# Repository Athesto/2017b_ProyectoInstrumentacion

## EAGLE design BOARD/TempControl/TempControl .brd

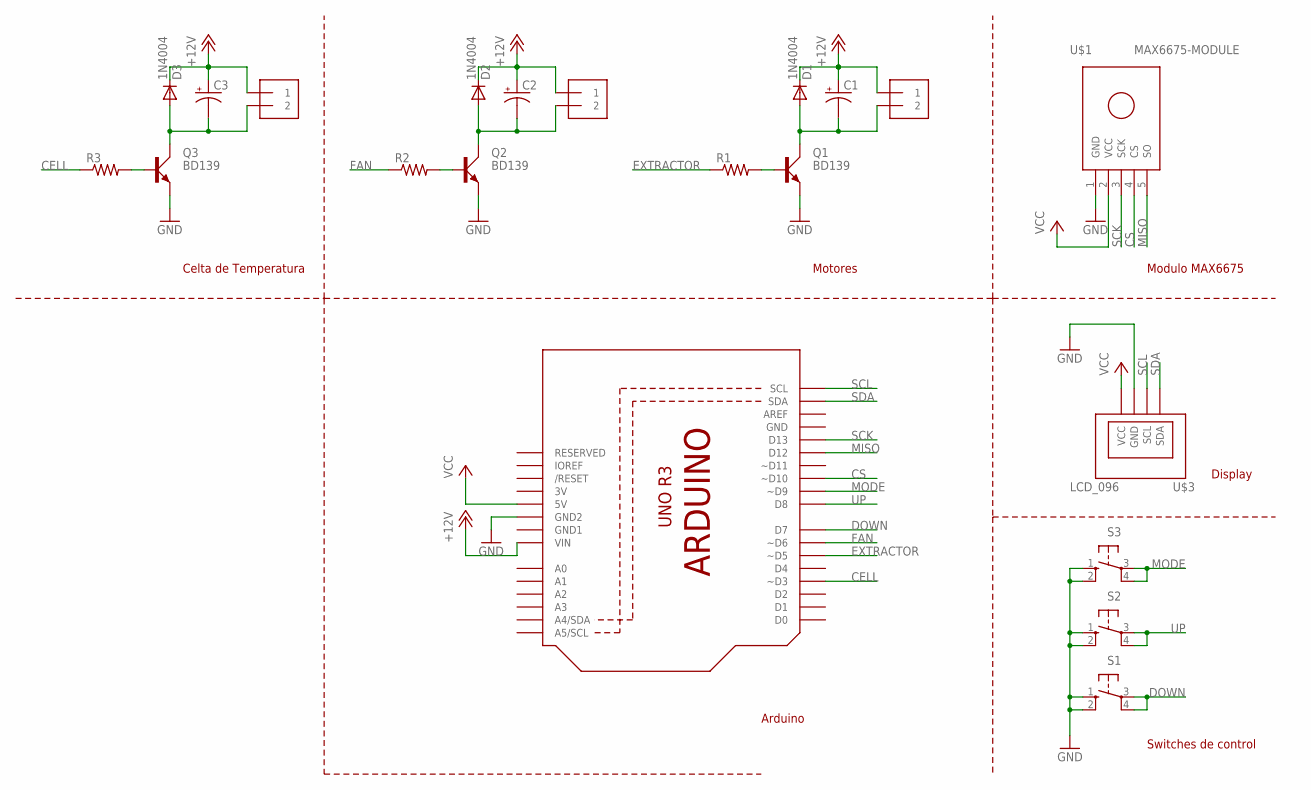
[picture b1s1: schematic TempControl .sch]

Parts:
C1, C2, C3: CPOL-USTT2D5; TT2D5
CELL: 1X2-3.5MM
D1, D2, D3: 1N4004; DO41-10
EXTRACTOR: 1X2-3.5MM
FAN: 1X2-3.5MM
Q1, Q2, Q3: BD139; TO126AV
R1, R2, R3: R-US_0207/10; 0207/10
S1, S2, S3: 40-XX-ROUND; B3F-40XX-ROUND
U1: ARDUINOR3-BPLACE
U$1: MAX6675-MODULE; FE05-1
U$3: LCD_096; LCD_096"

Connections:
3V: U1.3V
+12V: C1.+, C2.+, C3.+, CELL.1, D1.C, D2.C, D3.C, EXTRACTOR.1, FAN.1, U1.VIN
CELL: R3.1, U1.D3 (~D3)
CS: U1.D10 (~D10), U$1.4 (CS)
DOWN: S1.3, S1.4 (P1), U1.D7
EXTRACTOR: R1.1, U1.D5 (~D5)
FAN: R2.1, U1.D6 (~D6)
GND: Q1.E, Q2.E, Q3.E, S1.1 (S), S1.2 (S1), S2.1 (S), S2.2 (S1), S3.1 (S), S3.2 (S1), U1.GND, U1.GND2, U$1.1 (GND), U$3.P$2 (GND)
GND1: U1.GND1
MISO: U1.D12, U$1.5 (SO)
MODE: S3.3, S3.4 (P1), U1.D9 (~D9)
unnamed: C2.-, D2.A, FAN.2, Q2.C
unnamed: C1.-, D1.A, EXTRACTOR.2, Q1.C
unnamed: Q1.B, R1.2
unnamed: Q2.B, R2.2
unnamed: C3.-, CELL.2, D3.A, Q3.C
unnamed: Q3.B, R3.2
SCK: U1.D13, U$1.3 (SCK)
SCL: U1.SCL, U$3.P$3 (SCL)
SDA: U1.SDA, U$3.P$4 (SDA)
UP: S2.3, S2.4 (P1), U1.D8
VCC: U1.5V, U$1.2 (VCC), U$3.P$1 (VCC)

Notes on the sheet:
Modulo MAX6675
Switches de control
Display
Motores
Arduino
Celta de Temperatura

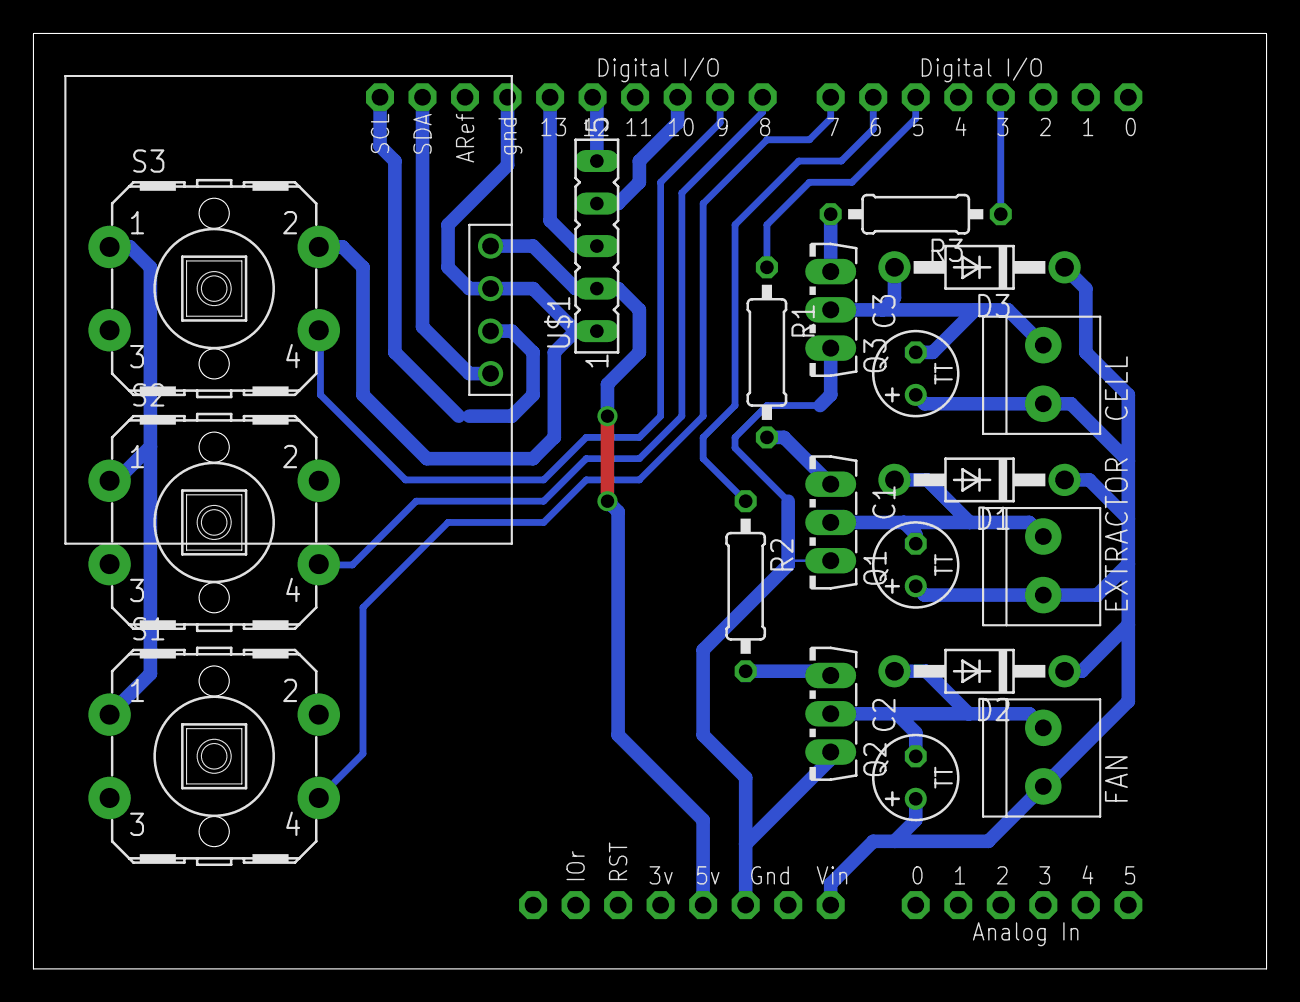
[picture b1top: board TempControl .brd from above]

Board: 2 copper layers, 73.7 x 55.9 mm, 21 parts (0 on the bottom side), 20 nets.

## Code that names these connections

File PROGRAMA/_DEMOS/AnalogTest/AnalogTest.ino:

#define cell 3
#define extractor 5
#define fan 6
double val;
void setup() {
  //Serial.begin(115200);
  //Serial.println("Arduino");

}

void loop() {
  //val= analogRead(A1);
  val += 0.01;
  if (val>1) val = 0;
  //Serial.println(val*100);
  analogWrite(cell,val*255);
  analogWrite(extractor,val*255);
  analogWrite(fan,val*255);
  delay(50);

}

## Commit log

2017-11-16 doc Folder
2017-11-16 Set theme jekyll-theme-slate
2017-11-16 WebPage
    - Se prueba la página
    - Se añade el título, descripción y tema
2017-11-16 Web: Development Section
    - Include favicon
2017-11-19 Firmware v0
2017-11-19 webedit
2017-11-25 Include Demo and library
2017-11-25 PCB file
2017-11-25 Web: BOM
    - Se hace la Galería
2017-11-25 Web: Galeria
    - Se cambió la posicion de las sección de desarrollo
    - update: imagen del esquemático
    - added: Novedades
2017-12-03 New WebPage
    www.peltierUA2017.tk
2017-12-03 miniors changes
2017-12-03 Demos
    - AnaogTest
    - DisplayTest
    - Timers
2017-12-03 webpage
2017-12-03 Published with https://stackedit.io/
2017-12-05 Webpage: New Name
2017-12-05 Program Working: v1
2017-12-05 Webpage: Transistor to BOM
2017-12-05 Test
2017-12-06 fix program
    El programa solo actualizaba si cambiaban el setpoint
